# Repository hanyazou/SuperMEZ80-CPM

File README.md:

# SuperMEZ80-CPM
SuperMEZ80-CPM is a Z80 mezzanine board for simple single board computer EMUZ80.
SuperMEZ80-CPM adds SRAM and SPI micro SD Card slot to the EMUZ80.
With SuperMEZ80-CPM, you can run CP/M 2.2 and 3.0 disk images from the z80pack on the EMUZ80.

SuperMEZ80-CPM Features
  * Simple 3-chip configuration of Z80, SRAM and PIC
  * CP/M 3.0 banked memory can be used
  * A retro appearance, all chips are DIP, no surface-mounted components

SuperMEZ80-CPM is derived from satoshiokue's MEZ80RAM board.
Both EMUZ80 and MEZ80RAM are very interesting ideas.

SuperMEZ80-CPM is similar to the SuperMEZ80-SPI.
SuperMEZ80-CPM is simpler board with fewer components by removing I/O expander chip from SuperMEZ80-SPI.

## Appearance
The blue board in the following photo is SuperMEZ80-CPM and the red board is EMUZ80.

## Components you need

### IC
  * 1 Z80 (DIP 40 pin) *1
  * 1 AS6C4008-55 SRAM 4Mbit (DIP 32 pin) *2
### Through hole components
  * 1 IC socket (DIP 40 pin)
  * 1 IC socket (DIP 32 pin)
  * 1 SD Card slot *3
  * 2 Capacitor 0.1uF
  * 3 LED
  * 3 Resistor 1.5K ohms 1/4W (the value of resistor will vary depending on the LED)
  * 1 Resistor array 10K ohms x8
  * 2 Pin header (0.1" pich 20x1 pin)
  * 1 Jumper cap and header (0.1" pich) *4
  * 1 Pin socket (0.1" pich 6x1 pin)

*1) Z80C0006 (6MHz) or higher are recomended

*2) 2Mbit (256KB) or more is required for CP/M 3.0.
CP/M 2.2 can still run with 512Kbit (64KB) or 1Mbit (128KB) RAM like TC551001.

*3) For the micro SD Card slot, use the one for Arduino as shown in the following page.

https://circuitdigest.com/microcontroller-projects/interfacing-micro-sd-card-module-with-arduino

*4) I use right angle pin header and jumper.
They are useful when I experiment external clock source. 
But you can omit them and just short RA3 - Z80 CLK with solder.

## Build Instructions

Due to some tall components, it is recommended to assemble them in the following order.

### Step 1: DIP 40 socket

### Step 2: pin headers

### Step 3: LED and passive components

### Step 4: DIP 32 socket and 6 pin socket

## (Optional) SD card slot modification
SD Card slot component in the market may have a right angle pin header.
As it is, it might be little bit ugly as shown in the picture.

I de-soldered and replaced the header and mounted the SD card slot in back of SuperMEZ80-CPM.

You can also mount the SD Card slot on the top of the board like SuperMEZ-SPI.

## References
### SuperMEZ80 (derived version for SuperMEZ80-CPM)
Use this firmware to PIC on the EMUZ80 board.

https://github.com/hanyazou/SuperMEZ80

### EMUZ80
https://vintagechips.wordpress.com/2022/03/05/emuz80_reference/

### z80pack
https://github.com/udo-munk/z80pack

### MEZ80RAM
https://github.com/satoshiokue/MEZ80RAM

### SuperMEZ80 (Satoshi Okue's original FW for MEZ80RAM)
https://github.com/satoshiokue/SuperMEZ80

### SuperMEZ80-SPI
https://github.com/hanyazou/SuperMEZ80-SPI

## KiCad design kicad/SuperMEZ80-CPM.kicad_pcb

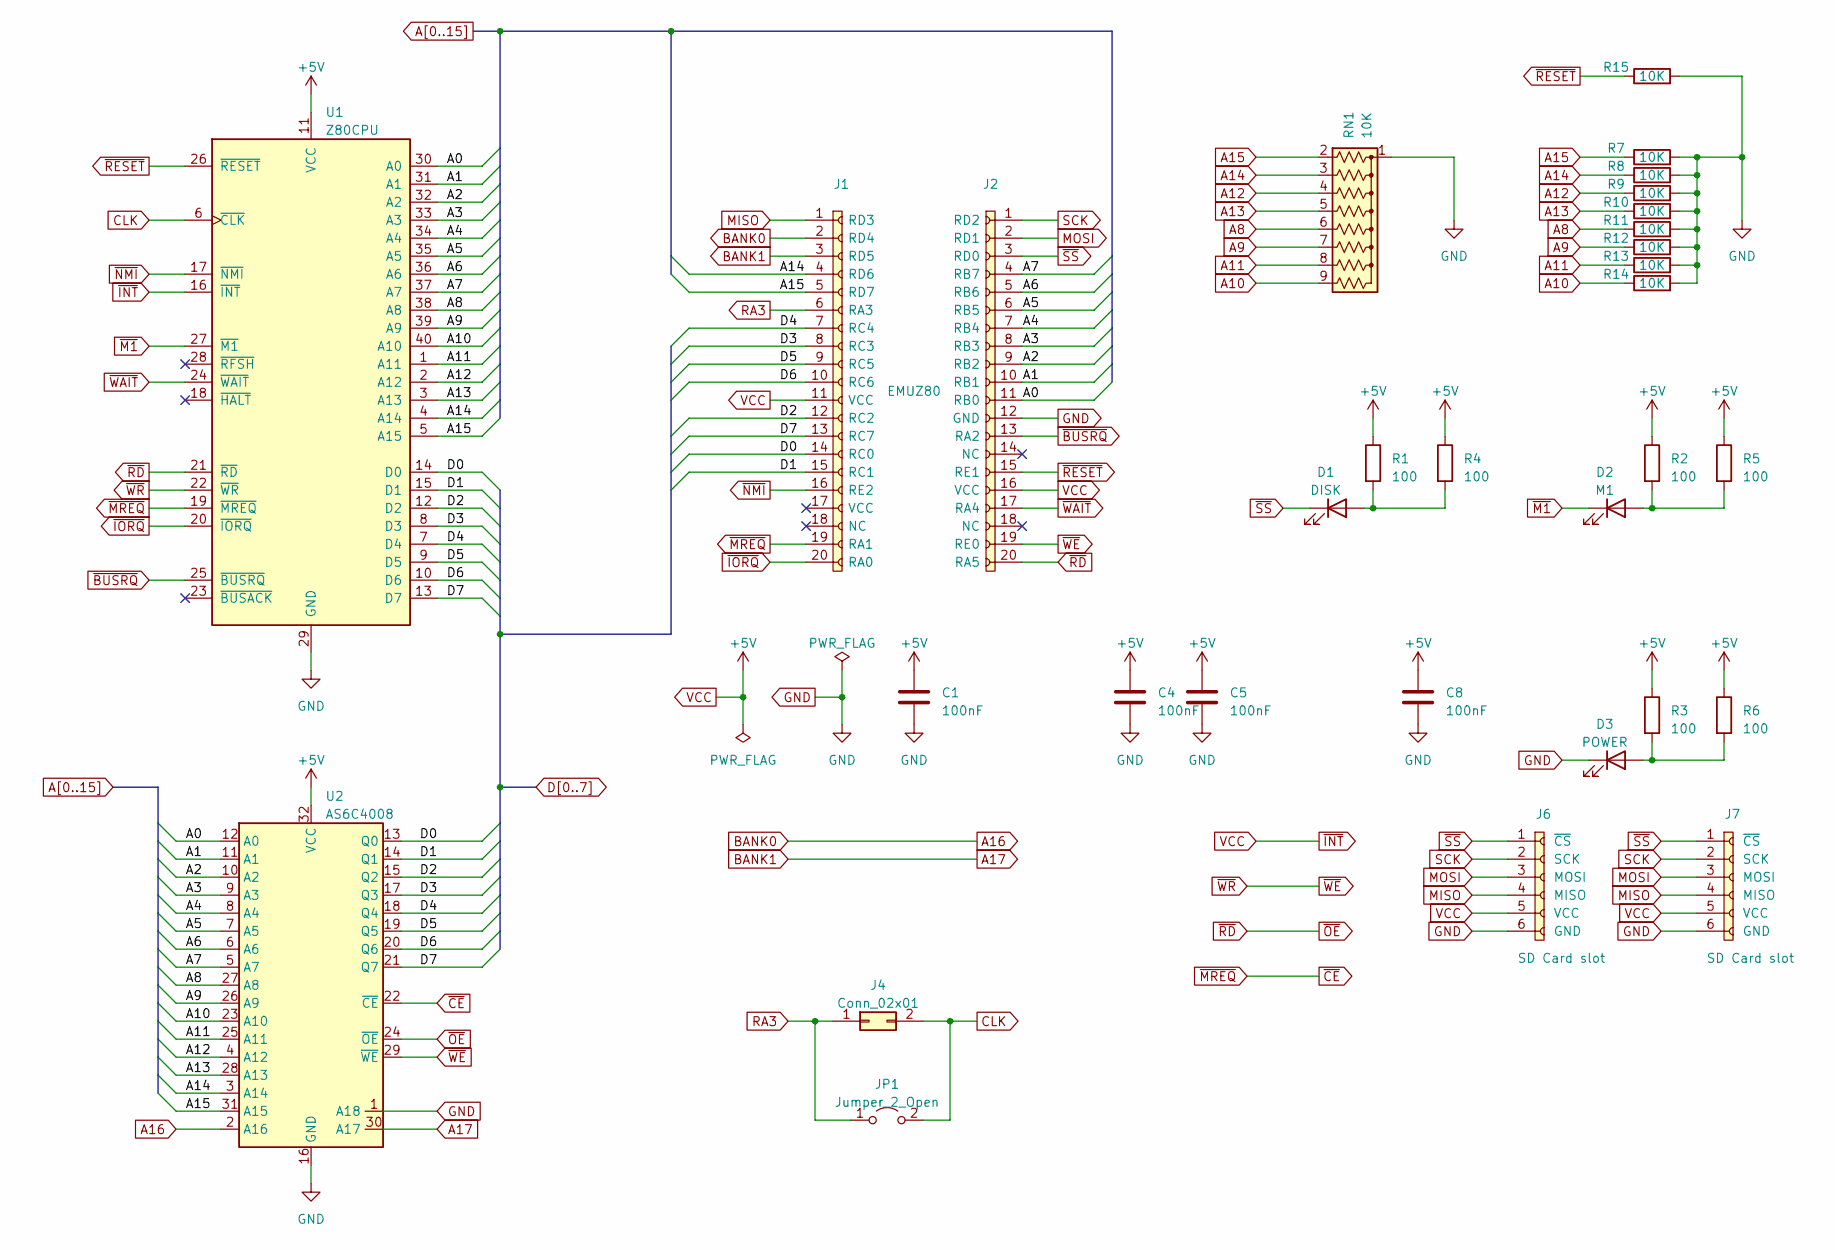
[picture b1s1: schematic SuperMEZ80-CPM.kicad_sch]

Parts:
C1, C4: 100nF; C_Disc_D4.3mm_W1.9mm_P5.00mm
C5, C8: 100nF; C_0603_1608Metric_Pad1.08x0.95mm_HandSolder
D1: DISK; LED_D1.8mm_W3.3mm_H2.4mm
D2: M1; LED_D1.8mm_W3.3mm_H2.4mm
D3: POWER; LED_D1.8mm_W3.3mm_H2.4mm
J1: EMUZ80_0; PinHeader_1x20_P2.54mm_Vertical
J2: EMUZ80; PinHeader_1x20_P2.54mm_Vertical
J4: Conn_02x01; PinHeader_1x02_P2.54mm_Vertical
J6, J7: SD Card slot; PinHeader_1x06_P2.54mm_Vertical
JP1: Jumper_2_Open; SolderJumper-2_P1.3mm_Open_RoundedPad1.0x1.5mm
R1, R2, R3: 100; R_Axial_DIN0204_L3.6mm_D1.6mm_P7.62mm_Horizontal
R4, R5, R6: 100; R_0603_1608Metric_Pad0.98x0.95mm_HandSolder
R7, R8, R9, R10, R11, R12, R13, R14, R15: 10K; R_0603_1608Metric_Pad0.98x0.95mm_HandSolder
RN1: 10K; R_Array_SIP9
U1: Z80CPU; DIP-40_W15.24mm
U2: AS6C4008; DIP-32_W15.24mm_Socket

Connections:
A0: J2.11 (RB0), U1.30 (A0), U2.12 (A0)
A1: J2.10 (RB1), U1.31 (A1), U2.11 (A1)
A2: J2.9 (RB2), U1.32 (A2), U2.10 (A2)
A3: J2.8 (RB3), U1.33 (A3), U2.9 (A3)
A4: J2.7 (RB4), U1.34 (A4), U2.8 (A4)
A5: J2.6 (RB5), U1.35 (A5), U2.7 (A5)
A6: J2.5 (RB6), U1.36 (A6), U2.6 (A6)
A7: J2.4 (RB7), U1.37 (A7), U2.5 (A7)
A8: R11.1, RN1.6 (R5), U1.38 (A8), U2.27 (A8)
A9: R12.1, RN1.7 (R6), U1.39 (A9), U2.26 (A9)
A10: R14.1, RN1.9 (R8), U1.40 (A10), U2.23 (A10)
A11: R13.1, RN1.8 (R7), U1.1 (A11), U2.25 (A11)
A12: R9.1, RN1.4 (R3), U1.2 (A12), U2.4 (A12)
A13: R10.1, RN1.5 (R4), U1.3 (A13), U2.28 (A13)
A14: J1.4 (RD6), R8.1, RN1.3 (R2), U1.4 (A14), U2.3 (A14)
A15: J1.5 (RD7), R7.1, RN1.2 (R1), U1.5 (A15), U2.31 (A15)
A16: J1.2 (RD4), U2.2 (A16)
A17: J1.3 (RD5), U2.30 (A17)
CLK: J4.2, JP1.2 (B), U1.6 (~CLK)
D0: J1.14 (RC0), U1.14 (D0), U2.13 (Q0)
D1: J1.15 (RC1), U1.15 (D1), U2.14 (Q1)
D2: J1.12 (RC2), U1.12 (D2), U2.15 (Q2)
D3: J1.8 (RC3), U1.8 (D3), U2.17 (Q3)
D4: J1.7 (RC4), U1.7 (D4), U2.18 (Q4)
D5: J1.9 (RC5), U1.9 (D5), U2.19 (Q5)
D6: J1.10 (RC6), U1.10 (D6), U2.20 (Q6)
D7: J1.13 (RC7), U1.13 (D7), U2.21 (Q7)
GND: C1.2, C4.2, C5.2, C8.2, D3.1 (K), J2.12 (GND), J6.6 (GND), J7.6 (GND), R7.2, R8.2, R9.2, R10.2, R11.2, R12.2, R13.2, R14.2, R15.2, RN1.1 (common), U1.29 (GND), U2.1 (A18), U2.16 (GND)
MISO: J1.1 (RD3), J6.4 (MISO), J7.4 (MISO)
MOSI: J2.2 (RD1), J6.3 (MOSI), J7.3 (MOSI)
unnamed: D1.2 (A), R1.2, R4.2
unnamed: D2.2 (A), R2.2, R5.2
unnamed: D3.2 (A), R3.2, R6.2
RA3: J1.6 (RA3), J4.1, JP1.1 (A)
SCK: J2.1 (RD2), J6.2 (SCK), J7.2 (SCK)
VCC: C1.1, C4.1, C5.1, C8.1, J1.11 (VCC), J2.16 (VCC), J6.5 (VCC), J7.5 (VCC), R1.1, R2.1, R3.1, R4.1, R5.1, R6.1, U1.11 (VCC), U1.16 (~INT), U2.32 (VCC)
~BUSRQ: J2.13 (RA2), U1.25 (~BUSRQ)
~CE: J1.19 (RA1), U1.19 (~MREQ), U2.22 (~CE)
~IORQ: J1.20 (RA0), U1.20 (~IORQ)
~M1: D2.1 (K), U1.27 (~M1)
~NMI: J1.16 (RE2), U1.17 (~NMI)
~OE: J2.20 (RA5), U1.21 (~RD), U2.24 (~OE)
~RESET: J2.15 (RE1), R15.1, U1.26 (~RESET)
~SS: D1.1 (K), J2.3 (RD0), J6.1 (~CS), J7.1 (~CS)
~WAIT: J2.17 (RA4), U1.24 (~WAIT)
~WE: J2.19 (RE0), U1.22 (~WR), U2.29 (~WE)

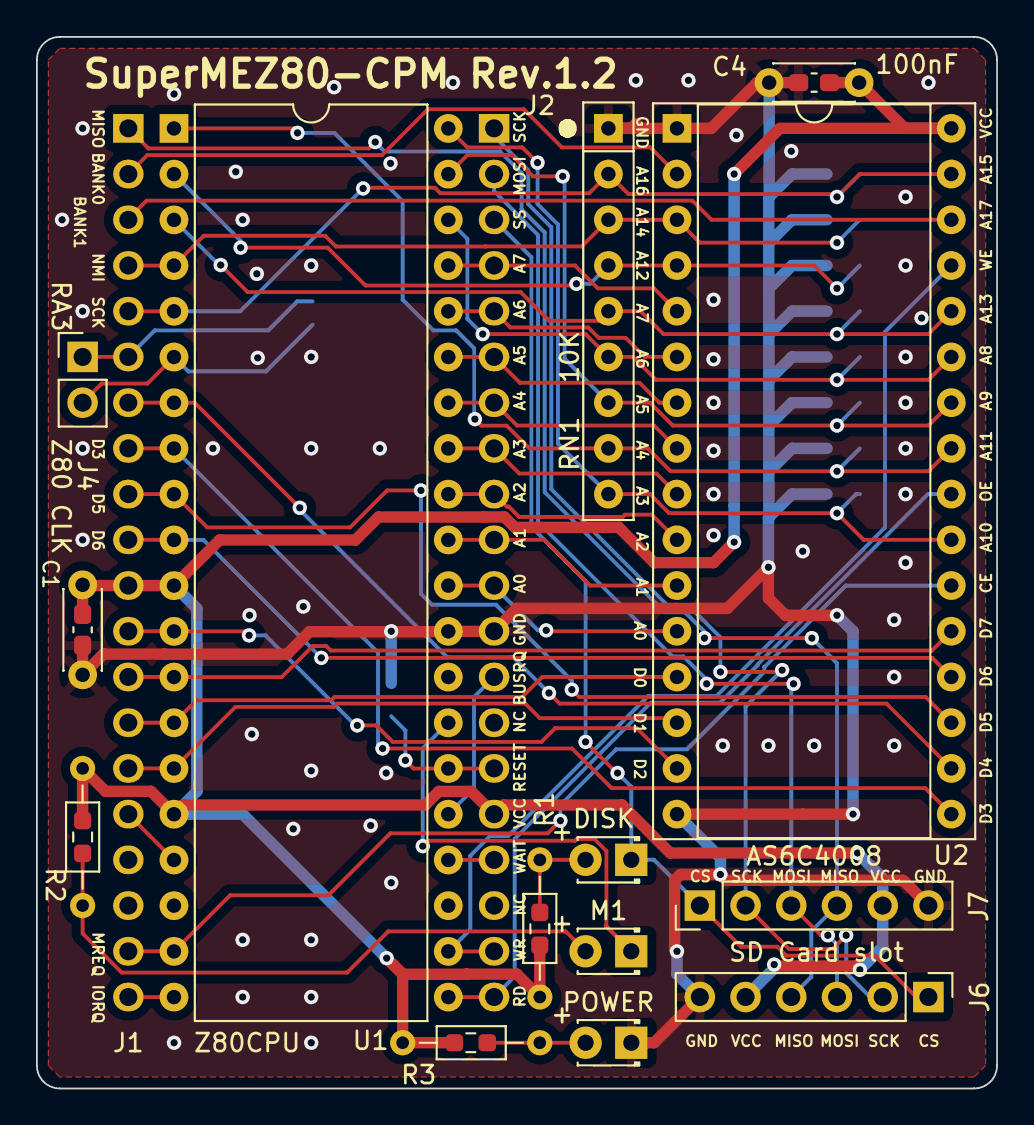
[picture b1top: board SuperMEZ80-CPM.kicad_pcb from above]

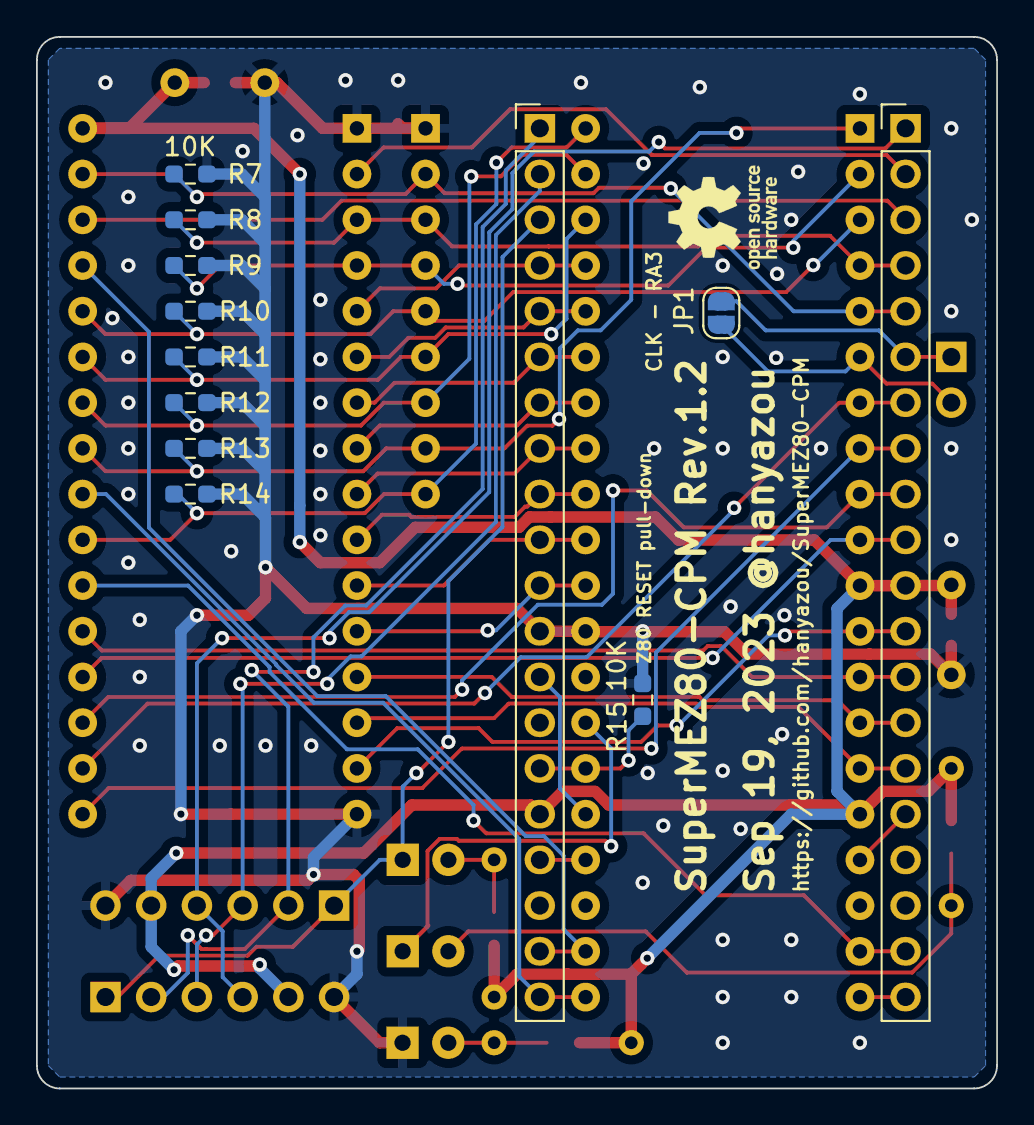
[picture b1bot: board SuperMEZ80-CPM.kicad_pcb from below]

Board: 2 copper layers, 53.3 x 58.4 mm, 31 parts (12 on the bottom side), 46 nets.

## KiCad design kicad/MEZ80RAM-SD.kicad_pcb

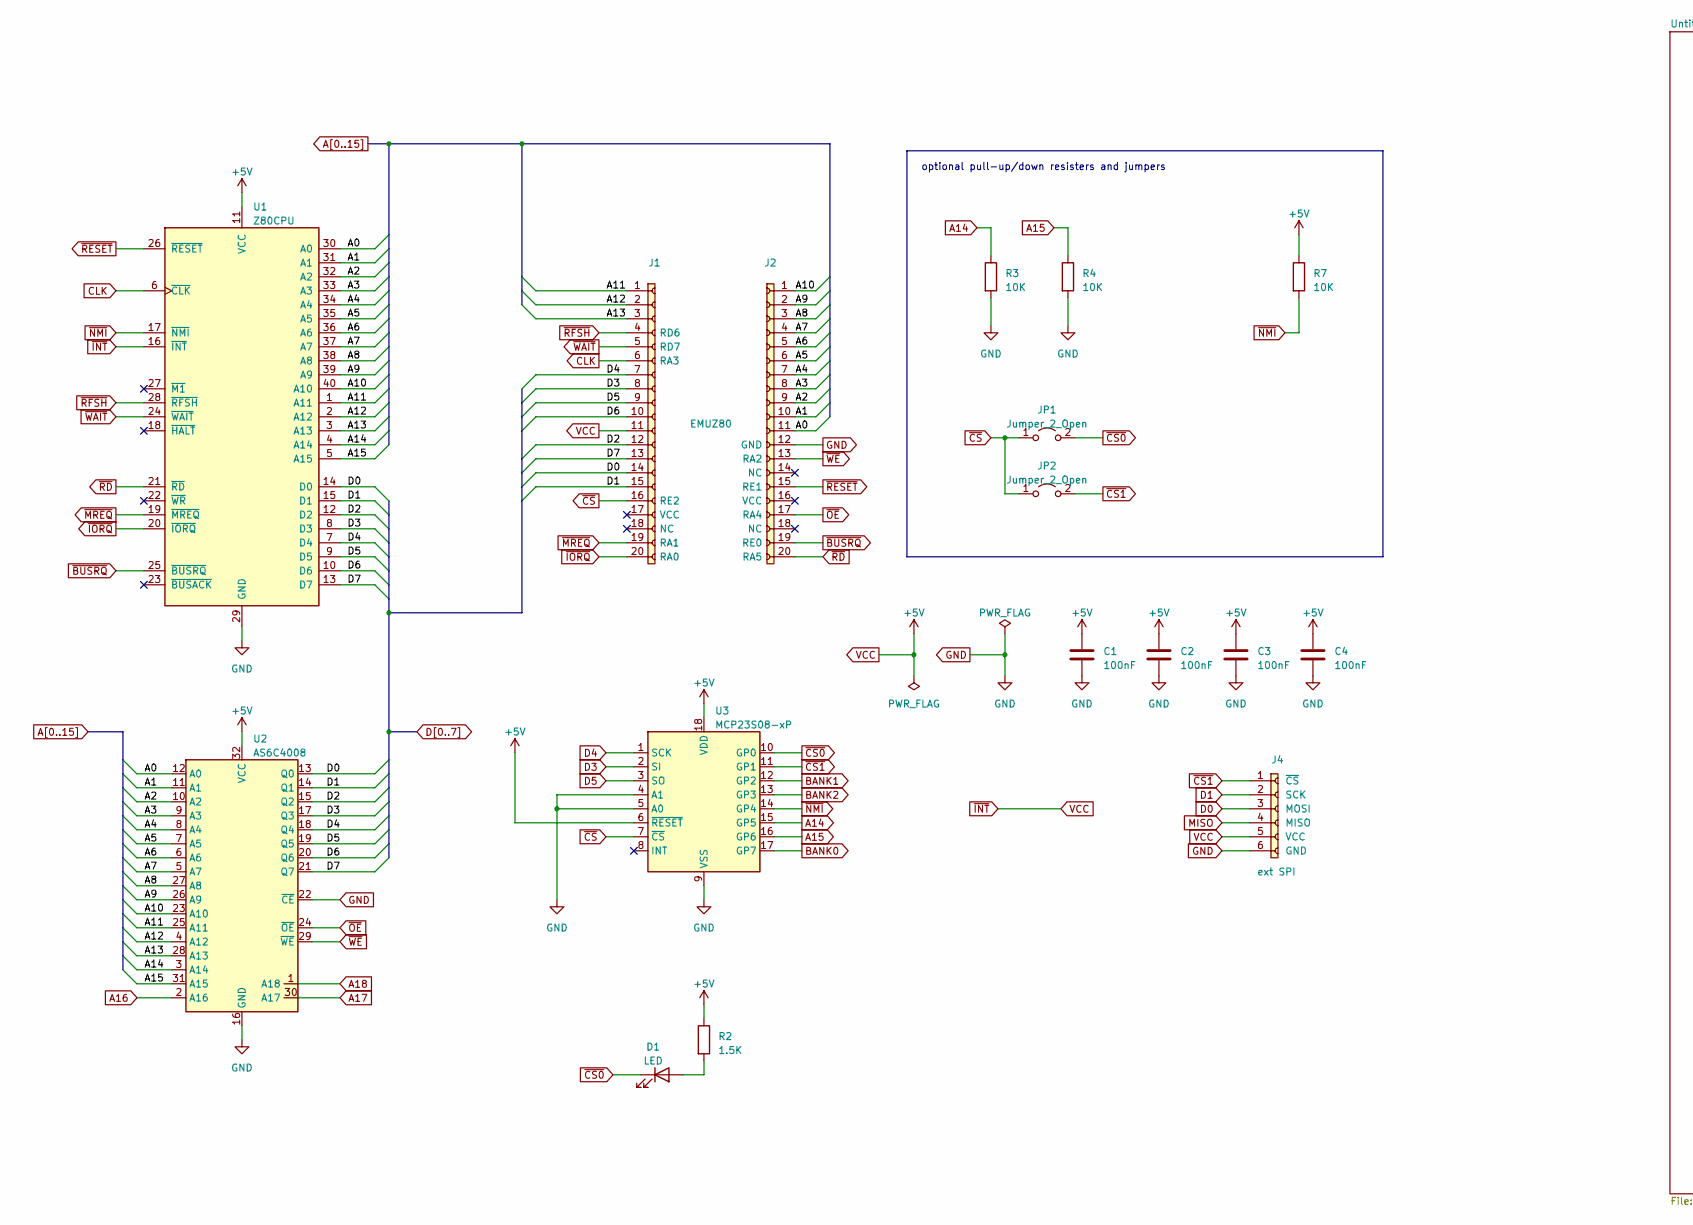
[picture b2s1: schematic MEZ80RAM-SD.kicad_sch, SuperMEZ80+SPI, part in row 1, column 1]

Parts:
C1, C2: 100nF; C_Disc_D4.3mm_W1.9mm_P5.00mm
C3, C4: 100nF; C_0603_1608Metric_Pad1.08x0.95mm_HandSolder
D1: LED; LED_D1.8mm_W3.3mm_H2.4mm
J1: EMUZ80_0; PinHeader_1x20_P2.54mm_Vertical
J2: EMUZ80; PinHeader_1x20_P2.54mm_Vertical
J4: ext SPI; PinHeader_1x06_P2.54mm_Vertical
JP1, JP2: Jumper_2_Open; SolderJumper-2_P1.3mm_Open_TrianglePad1.0x1.5mm
R2: 1.5K; R_Axial_DIN0204_L3.6mm_D1.6mm_P7.62mm_Horizontal
R3, R4, R7: 10K; R_0603_1608Metric_Pad0.98x0.95mm_HandSolder
U1: Z80CPU; DIP-40_W15.24mm
U2: AS6C4008; DIP-32_W15.24mm_Socket
U3: MCP23S08-xP; DIP-18_W7.62mm

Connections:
A0: J2.11, U1.30 (A0), U2.12 (A0)
A1: J2.10, U1.31 (A1), U2.11 (A1)
A2: J2.9, U1.32 (A2), U2.10 (A2)
A3: J2.8, U1.33 (A3), U2.9 (A3)
A4: J2.7, U1.34 (A4), U2.8 (A4)
A5: J2.6, U1.35 (A5), U2.7 (A5)
A6: J2.5, U1.36 (A6), U2.6 (A6)
A7: J2.4, U1.37 (A7), U2.5 (A7)
A8: J2.3, U1.38 (A8), U2.27 (A8)
A9: J2.2, U1.39 (A9), U2.26 (A9)
A10: J2.1, U1.40 (A10), U2.23 (A10)
A11: J1.1, U1.1 (A11), U2.25 (A11)
A12: J1.2, U1.2 (A12), U2.4 (A12)
A13: J1.3, U1.3 (A13), U2.28 (A13)
A14: R3.1, U1.4 (A14), U2.3 (A14), U3.15 (GP5); also elsewhere on the board
A15: R4.1, U1.5 (A15), U2.31 (A15), U3.16 (GP6); also elsewhere on the board
A16: U2.2 (A16); also elsewhere on the board
A17: U2.30 (A17); also elsewhere on the board
A18: U2.1 (A18); also elsewhere on the board
BANK0: U3.17 (GP7); also elsewhere on the board
BANK1: U3.12 (GP2); also elsewhere on the board
BANK2: U3.13 (GP3); also elsewhere on the board
CLK: J1.6 (RA3), U1.6 (~CLK)
D0: J1.14, J4.3 (MOSI), U1.14 (D0), U2.13 (Q0); also elsewhere on the board
D1: J1.15, J4.2 (SCK), U1.15 (D1), U2.14 (Q1); also elsewhere on the board
D3: J1.8, U1.8 (D3), U2.17 (Q3), U3.2 (SI)
D4: J1.7, U1.7 (D4), U2.18 (Q4), U3.1 (SCK)
D5: J1.9, U1.9 (D5), U2.19 (Q5), U3.3 (SO)
D6: J1.10, U1.10 (D6), U2.20 (Q6)
D7: J1.13, U1.13 (D7), U2.21 (Q7)
GND: C1.2, C2.2, C3.2, C4.2, J2.12 (GND), J4.6 (GND), R3.2, R4.2, U1.29 (GND), U2.16 (GND), U2.22 (~CE), U3.4 (A1), U3.5 (A0), U3.9 (VSS); also elsewhere on the board
unnamed 31: D1.2 (A), R2.2; also elsewhere on the board
VCC: C1.1, C2.1, C3.1, C4.1, J1.11, J4.5 (VCC), R2.1, R7.1, U1.11 (VCC), U1.16 (~INT), U2.32 (VCC), U3.6 (~RESET), U3.18 (VDD); also elsewhere on the board
~BUSRQ: J2.19 (RE0), U1.25 (~BUSRQ)
~CS1: J4.1 (~CS), JP2.2 (B), U3.11 (GP1)
~IORQ: J1.20 (RA0), U1.20 (~IORQ)
~MREQ: J1.19 (RA1), U1.19 (~MREQ)
~NMI: R7.2, U1.17 (~NMI), U3.14 (GP4)
~OE: J2.17 (RA4), U2.24 (~OE)
~RD: J2.20 (RA5), U1.21 (~RD)
~RESET: J2.15 (RE1), U1.26 (~RESET)
~RFSH: J1.4 (RD6), U1.28 (~RFSH)
~WAIT: J1.5 (RD7), U1.24 (~WAIT)
~WE: J2.13 (RA2), U2.29 (~WE)

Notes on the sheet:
optional pull-up/down resisters and jumpers

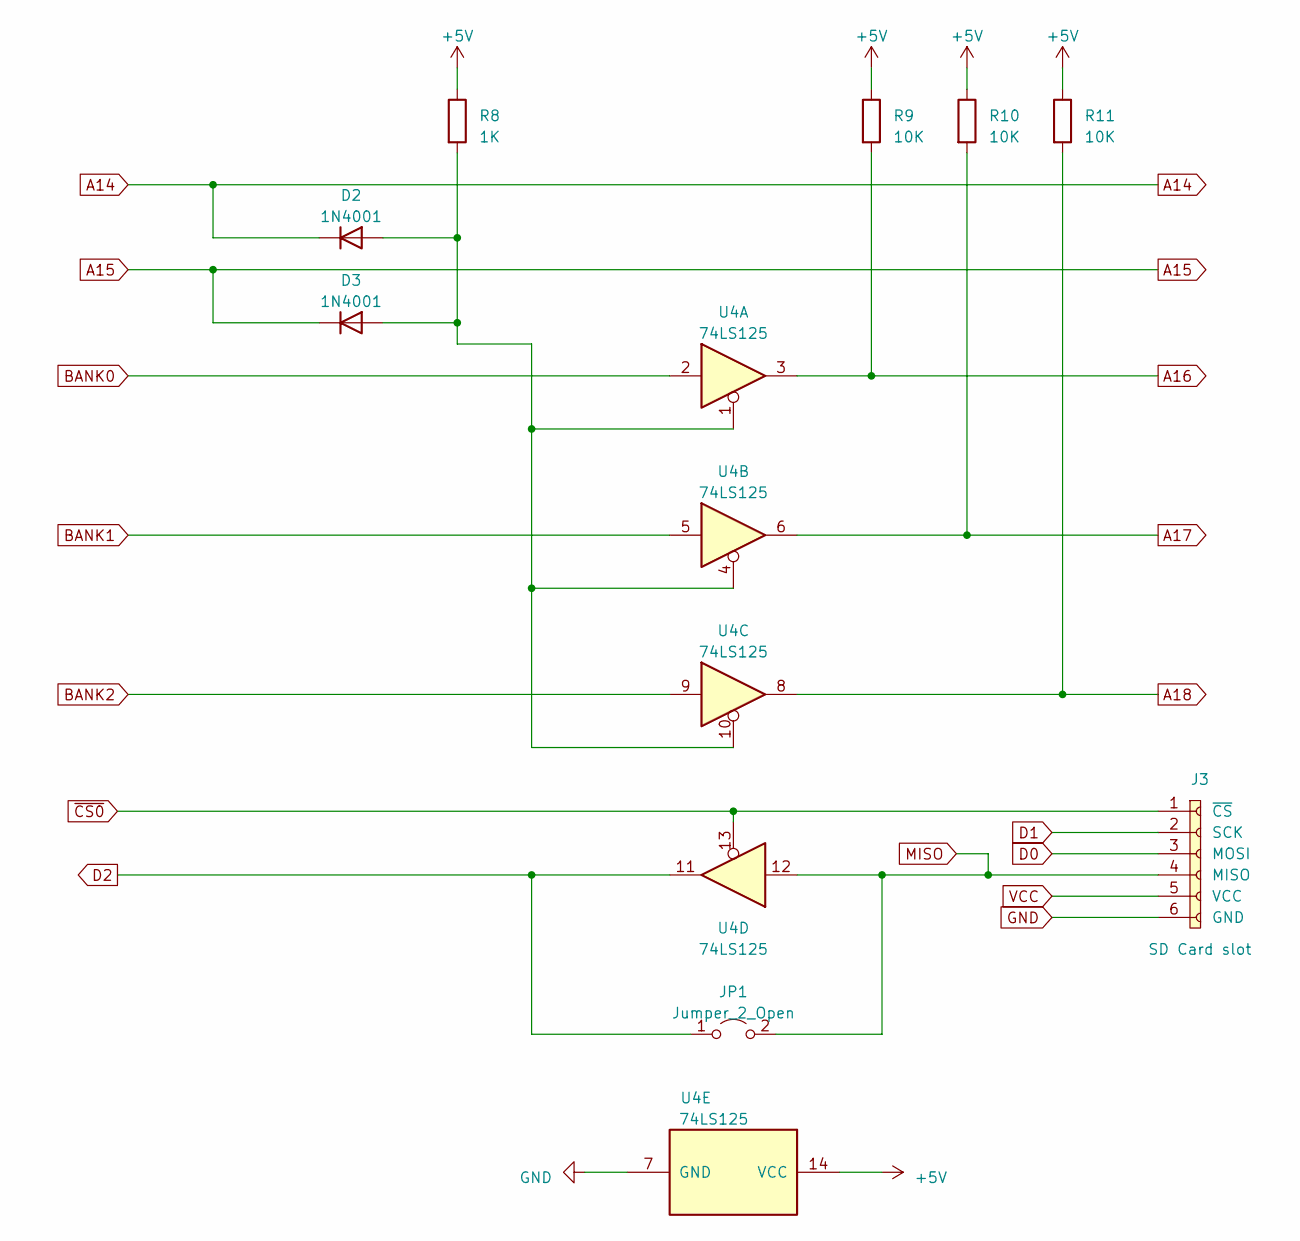
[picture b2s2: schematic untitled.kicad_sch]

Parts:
D2, D3: 1N4001; D_0805_2012Metric_Pad1.15x1.40mm_HandSolder
J3: SD Card slot; PinSocket_1x06_P2.54mm_Vertical
JP1: Jumper_2_Open; SolderJumper-2_P1.3mm_Open_TrianglePad1.0x1.5mm
R8: 1K; R_0603_1608Metric_Pad0.98x0.95mm_HandSolder
R9, R10, R11: 10K; R_0603_1608Metric_Pad0.98x0.95mm_HandSolder
U4: 74LS125; DIP-14_W7.62mm

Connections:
A14: D2.1 (K); also elsewhere on the board
A15: D3.1 (K); also elsewhere on the board
A16: R9.2, U4.3; also elsewhere on the board
A17: R10.2, U4.6; also elsewhere on the board
A18: R11.2, U4.8; also elsewhere on the board
BANK0: U4.2; also elsewhere on the board
BANK1: U4.5; also elsewhere on the board
BANK2: U4.9; also elsewhere on the board
GND: U4.7 (GND); also elsewhere on the board
unnamed: D2.2 (A), D3.2 (A), R8.2, U4.1, U4.4, U4.10
VCC: R8.1, R9.1, R10.1, R11.1, U4.14 (VCC); also elsewhere on the board

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
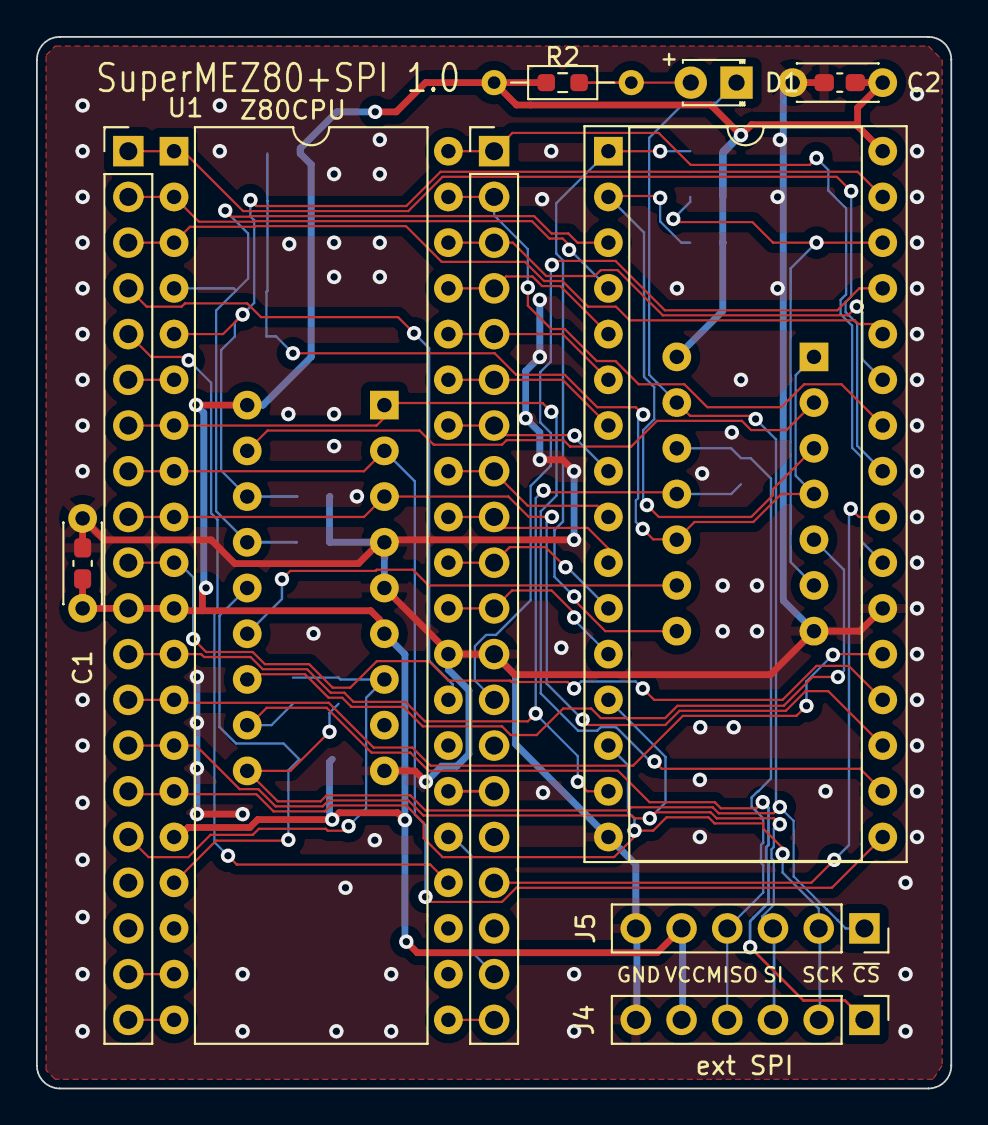
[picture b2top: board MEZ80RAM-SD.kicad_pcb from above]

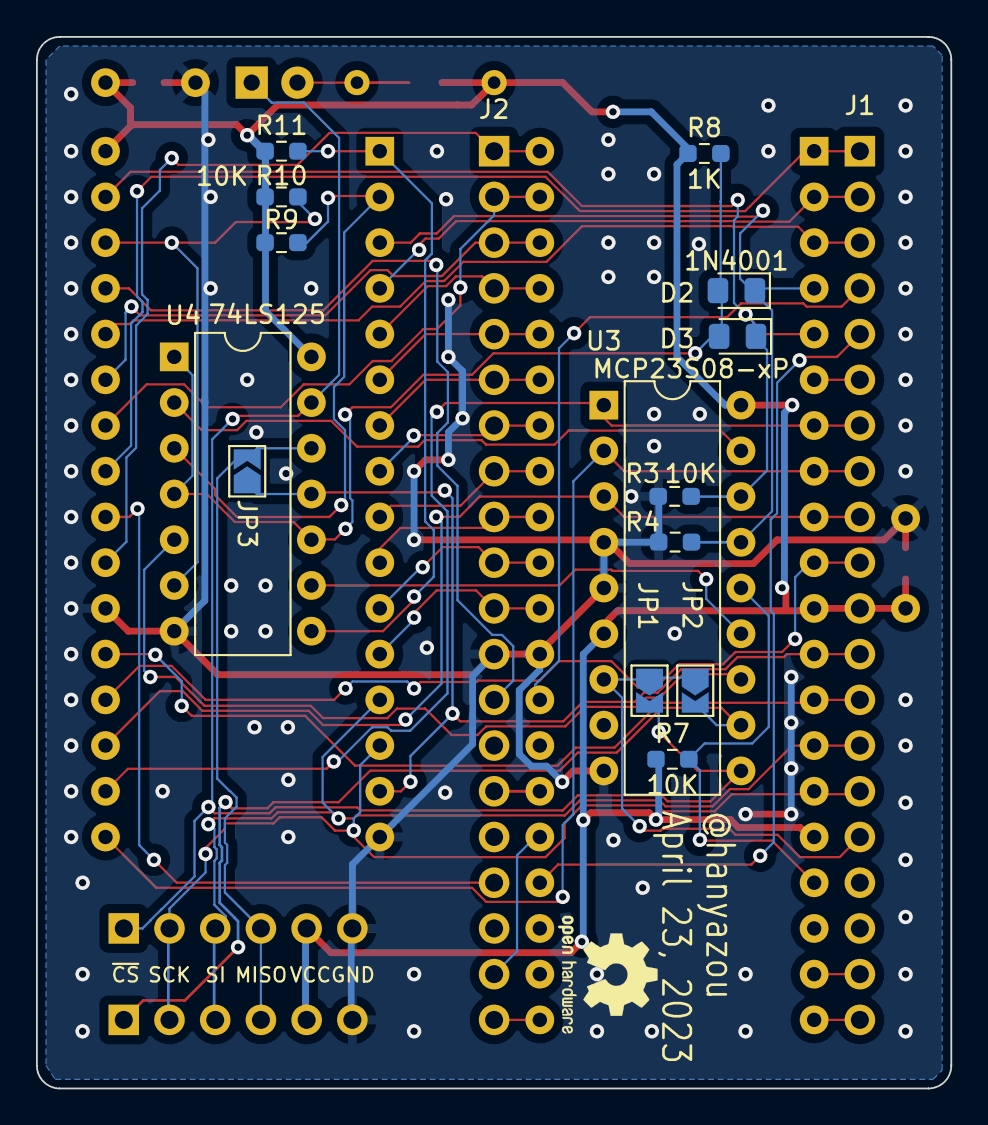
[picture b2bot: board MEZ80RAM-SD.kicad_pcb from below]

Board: 2 copper layers, 50.8 x 58.4 mm, 27 parts (14 on the bottom side), 49 nets.

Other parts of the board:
J5: SD Card slot; PinSocket_1x06_P2.54mm_Vertical
JP3: Jumper_2_Open; SolderJumper-2_P1.3mm_Open_TrianglePad1.0x1.5mm
R2#2: 1.5K; R_0603_1608Metric_Pad0.98x0.95mm_HandSolder

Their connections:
D0: J5.3 (MOSI); also elsewhere on the board
D1: J5.2 (SCK); also elsewhere on the board
GND: J5.6 (GND); also elsewhere on the board
unnamed 31: R2#2.2; also elsewhere on the board
VCC: J5.5 (VCC), R2#2.1; also elsewhere on the board

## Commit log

2023-05-01 Add SuperMEZ80+SPI 1.0
2023-05-01 Add images
2023-05-06 Fix LED registor value, diode type and so on
2023-07-09 Add first version of SuperMEZ80-CPM PCB
2023-08-17 Add SuperMEZ80-CPM version 1.0
2023-09-02 Add SuperMEZ80-CPM version 1.1 and update README.md
2023-09-20 Add SuperMEZ80-CPM version 1.2
